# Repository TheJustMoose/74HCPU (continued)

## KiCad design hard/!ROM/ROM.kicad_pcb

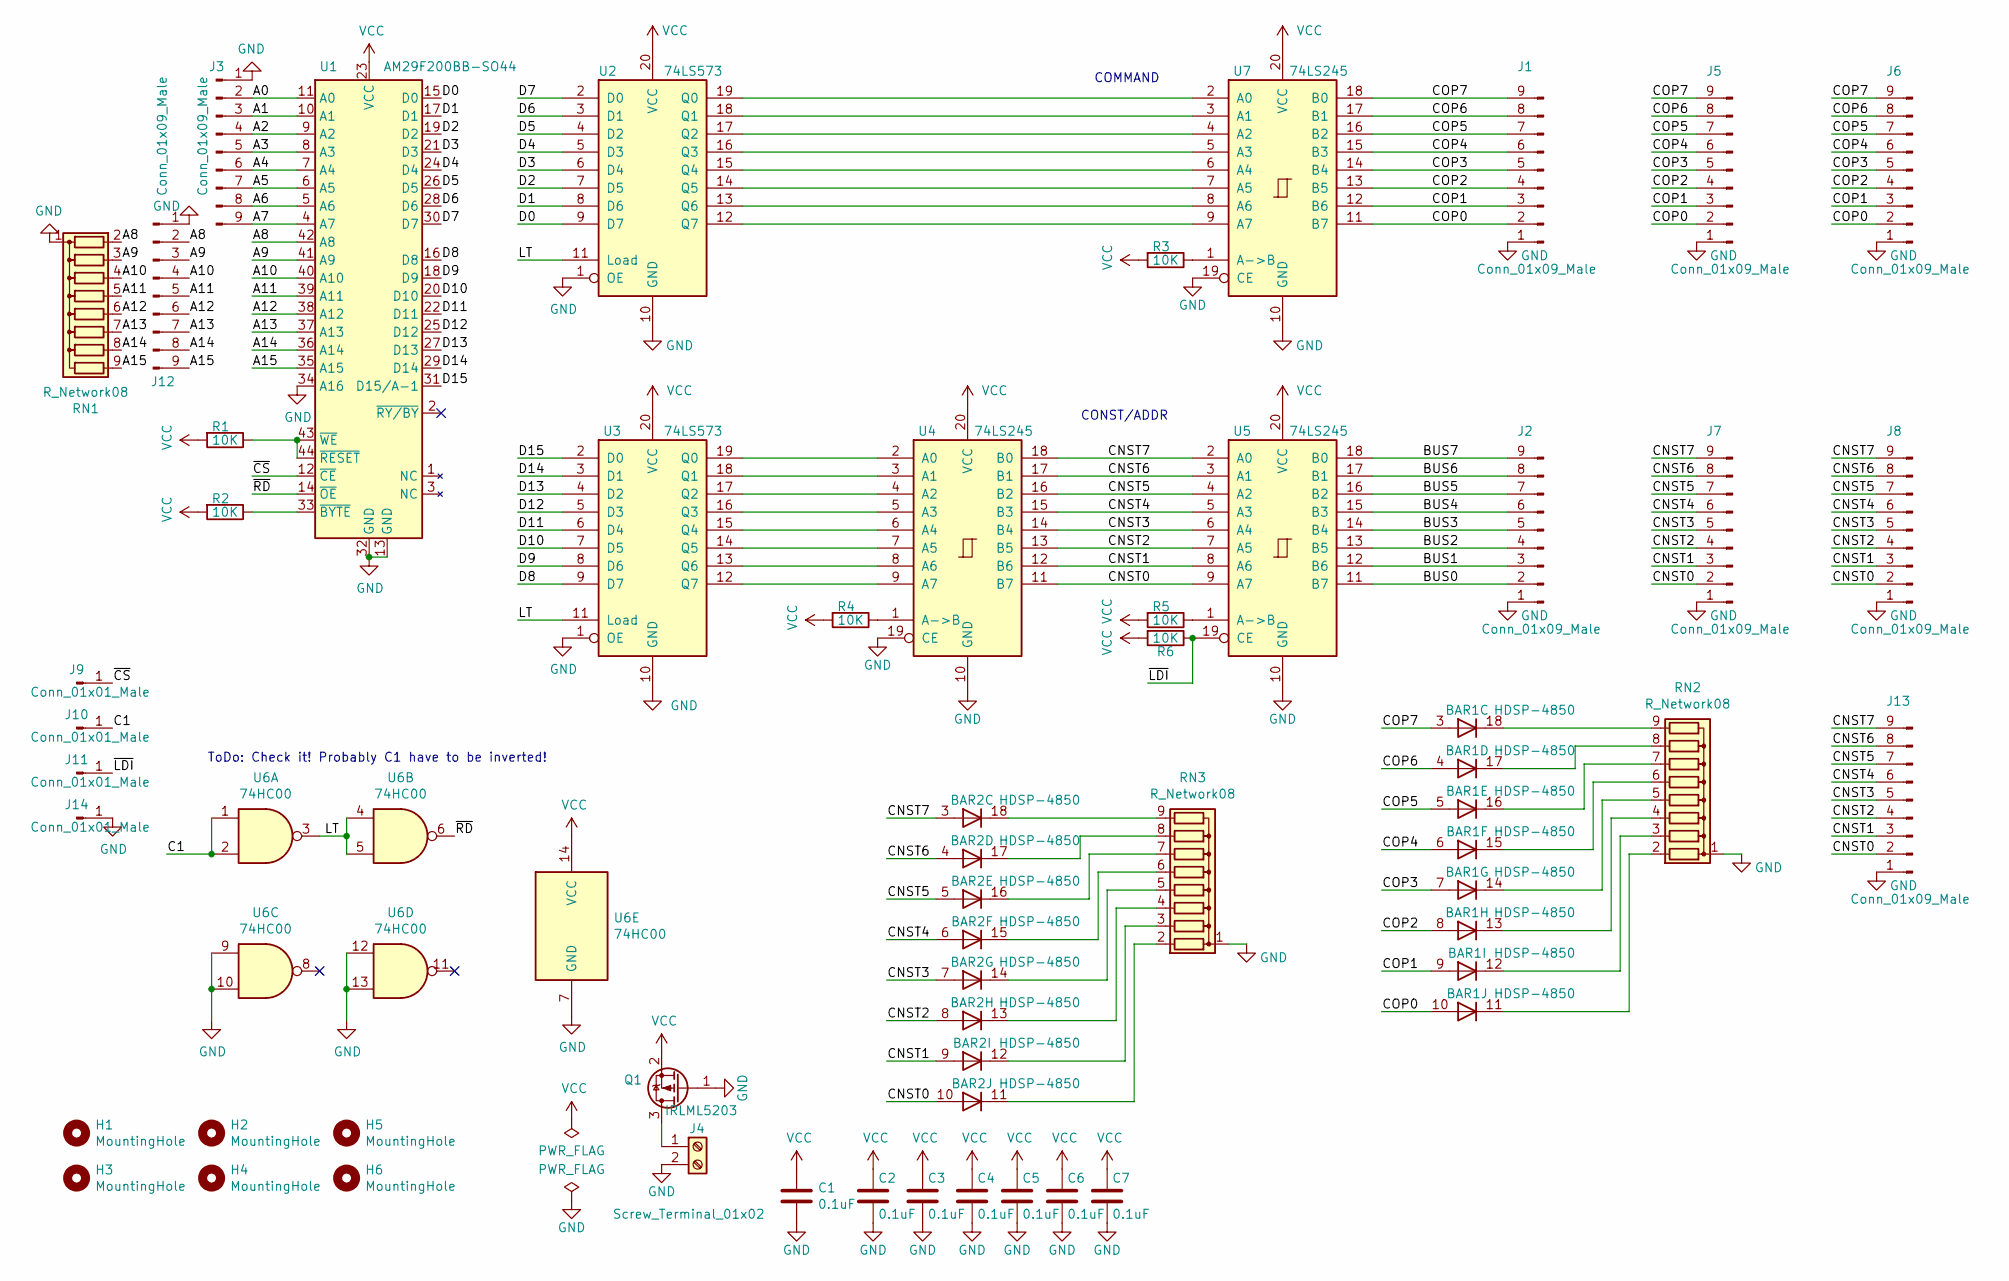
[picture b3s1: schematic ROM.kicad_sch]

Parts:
BAR1, BAR2: HDSP-4850
C1: 0.1uF; C_Rect_L24.0mm_W7.0mm_P22.50mm_MKT
C2, C3, C4, C5, C6, C7: 0.1uF; C_Disc_D7.5mm_W5.0mm_P7.50mm
H1, H2, H3, H4, H5, H6: MountingHole; MountingHole_3.2mm_M3
J1, J2, J3, J5, J6, J7, J8, J12, J13: Conn_01x09_Male; PinHeader_1x09_P2.54mm_Vertical
J4: Screw_Terminal_01x02; TerminalBlock_Phoenix_PT-1,5-2-5.0-H_1x02_P5.00mm_Horizontal
J9, J10, J11, J14: Conn_01x01_Male; PinHeader_1x01_P2.54mm_Vertical
Q1: IRLML5203; SOT-23
R1, R2, R3, R4, R5, R6: 10K; R_0805_2012Metric_Pad1.20x1.40mm_HandSolder
RN1, RN2, RN3: R_Network08; R_Array_SIP9
U1: AM29F200BB-SO44; DIP-44_W15.24mm
U2, U3: 74LS573; DIP-20_W7.62mm
U4, U5, U7: 74LS245; DIP-20_W7.62mm
U6: 74HC00; DIP-14_W7.62mm

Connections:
/A0: J3.2, U1.11 (A0)
/A1: J3.3, U1.10 (A1)
/A2: J3.4, U1.9 (A2)
/A3: J3.5, U1.8 (A3)
/A4: J3.6, U1.7 (A4)
/A5: J3.7, U1.6 (A5)
/A6: J3.8, U1.5 (A6)
/A7: J3.9, U1.4 (A7)
/A8: J12.2, RN1.2 (R1), U1.42 (A8)
/A9: J12.3, RN1.3 (R2), U1.41 (A9)
/A10: J12.4, RN1.4 (R3), U1.40 (A10)
/A11: J12.5, RN1.5 (R4), U1.39 (A11)
/A12: J12.6, RN1.6 (R5), U1.38 (A12)
/A13: J12.7, RN1.7 (R6), U1.37 (A13)
/A14: J12.8, RN1.8 (R7), U1.36 (A14)
/A15: J12.9, RN1.9 (R8), U1.35 (A15)
/BUS0: J2.2, U5.11 (B7)
/BUS1: J2.3, U5.12 (B6)
/BUS2: J2.4, U5.13 (B5)
/BUS3: J2.5, U5.14 (B4)
/BUS4: J2.6, U5.15 (B3)
/BUS5: J2.7, U5.16 (B2)
/BUS6: J2.8, U5.17 (B1)
/BUS7: J2.9, U5.18 (B0)
/C1: J10.1, U6.1, U6.2
/CNST0: BAR2.10 (A), J7.2, J8.2, J13.2, U4.11 (B7), U5.9 (A7)
/CNST1: BAR2.9 (A), J7.3, J8.3, J13.3, U4.12 (B6), U5.8 (A6)
/CNST2: BAR2.8 (A), J7.4, J8.4, J13.4, U4.13 (B5), U5.7 (A5)
/CNST3: BAR2.7 (A), J7.5, J8.5, J13.5, U4.14 (B4), U5.6 (A4)
/CNST4: BAR2.6 (A), J7.6, J8.6, J13.6, U4.15 (B3), U5.5 (A3)
/CNST5: BAR2.5 (A), J7.7, J8.7, J13.7, U4.16 (B2), U5.4 (A2)
/CNST6: BAR2.4 (A), J7.8, J8.8, J13.8, U4.17 (B1), U5.3 (A1)
/CNST7: BAR2.3 (A), J7.9, J8.9, J13.9, U4.18 (B0), U5.2 (A0)
/COP0: BAR1.10 (A), J1.2, J5.2, J6.2, U7.11 (B7)
/COP1: BAR1.9 (A), J1.3, J5.3, J6.3, U7.12 (B6)
/COP2: BAR1.8 (A), J1.4, J5.4, J6.4, U7.13 (B5)
/COP3: BAR1.7 (A), J1.5, J5.5, J6.5, U7.14 (B4)
/COP4: BAR1.6 (A), J1.6, J5.6, J6.6, U7.15 (B3)
/COP5: BAR1.5 (A), J1.7, J5.7, J6.7, U7.16 (B2)
/COP6: BAR1.4 (A), J1.8, J5.8, J6.8, U7.17 (B1)
/COP7: BAR1.3 (A), J1.9, J5.9, J6.9, U7.18 (B0)
/D0: U1.15 (D0), U2.9 (D7)
/D1: U1.17 (D1), U2.8 (D6)
/D2: U1.19 (D2), U2.7 (D5)
/D3: U1.21 (D3), U2.6 (D4)
/D4: U1.24 (D4), U2.5 (D3)
/D5: U1.26 (D5), U2.4 (D2)
/D6: U1.28 (D6), U2.3 (D1)
/D7: U1.30 (D7), U2.2 (D0)
/D8: U1.16 (D8), U3.9 (D7)
/D9: U1.18 (D9), U3.8 (D6)
/D10: U1.20 (D10), U3.7 (D5)
/D11: U1.22 (D11), U3.6 (D4)
/D12: U1.25 (D12), U3.5 (D3)
/D13: U1.27 (D13), U3.4 (D2)
/D14: U1.29 (D14), U3.3 (D1)
/D15: U1.31 (D15/A-1), U3.2 (D0)
/LT: U2.11 (Load), U3.11 (Load), U6.3, U6.4, U6.5
/~CS: J9.1, U1.12 (~CE)
/~LDI: J11.1, R6.1, U5.19 (CE)
/~RD: U1.14 (~OE), U6.6
GND: C1.2, C2.2, C3.2, C4.2, C5.2, C6.2, C7.2, J1.1, J2.1, J3.1, J4.2, J5.1, J6.1, J7.1, J8.1, J12.1, J13.1, J14.1, Q1.1 (G), RN1.1 (common), RN2.1 (common), RN3.1 (common), U1.13 (GND), U1.32 (GND), U1.34 (A16), U2.1 (OE), U2.10 (GND), U3.1 (OE), U3.10 (GND), U4.10 (GND), U4.19 (CE), U5.10 (GND), U6.7 (GND), U6.9, U6.10, U6.12, U6.13, U7.10 (GND), U7.19 (CE)
unnamed: BAR1.11 (K), RN2.2 (R1)
unnamed: BAR1.12 (K), RN2.3 (R2)
unnamed: BAR1.13 (K), RN2.4 (R3)
unnamed: BAR1.14 (K), RN2.5 (R4)
unnamed: BAR1.15 (K), RN2.6 (R5)
unnamed: BAR1.16 (K), RN2.7 (R6)
unnamed: BAR1.17 (K), RN2.8 (R7)
unnamed: BAR1.18 (K), RN2.9 (R8)
unnamed: BAR2.11 (K), RN3.2 (R1)
unnamed: BAR2.12 (K), RN3.3 (R2)
unnamed: BAR2.13 (K), RN3.4 (R3)
unnamed: BAR2.14 (K), RN3.5 (R4)
unnamed: BAR2.15 (K), RN3.6 (R5)
unnamed: BAR2.16 (K), RN3.7 (R6)
unnamed: BAR2.17 (K), RN3.8 (R7)
unnamed: BAR2.18 (K), RN3.9 (R8)
unnamed: J4.1, Q1.3 (D)
unnamed: R1.1, U1.43 (~WE), U1.44 (~RESET)
unnamed: R2.1, U1.33 (~BYTE)
unnamed: R3.1, U7.1 (A->B)
unnamed: R4.1, U4.1 (A->B)
unnamed: R5.1, U5.1 (A->B)
unnamed: U2.12 (Q7), U7.9 (A7)
unnamed: U2.13 (Q6), U7.8 (A6)
unnamed: U2.14 (Q5), U7.7 (A5)
unnamed: U2.15 (Q4), U7.6 (A4)
unnamed: U2.16 (Q3), U7.5 (A3)
unnamed: U2.17 (Q2), U7.4 (A2)
unnamed: U2.18 (Q1), U7.3 (A1)
unnamed: U2.19 (Q0), U7.2 (A0)
unnamed: U3.12 (Q7), U4.9 (A7)
unnamed: U3.13 (Q6), U4.8 (A6)
unnamed: U3.14 (Q5), U4.7 (A5)
unnamed: U3.15 (Q4), U4.6 (A4)
unnamed: U3.16 (Q3), U4.5 (A3)
unnamed: U3.17 (Q2), U4.4 (A2)
unnamed: U3.18 (Q1), U4.3 (A1)
unnamed: U3.19 (Q0), U4.2 (A0)
VCC: C1.1, C2.1, C3.1, C4.1, C5.1, C6.1, C7.1, Q1.2 (S), R1.2, R2.2, R3.2, R4.2, R5.2, R6.2, U1.23 (VCC), U2.20 (VCC), U3.20 (VCC), U4.20 (VCC), U5.20 (VCC), U6.14 (VCC), U7.20 (VCC)

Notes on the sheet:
CONST/ADDR
ToDo: Check it! Probably C1 have to be inverted!
COMMAND

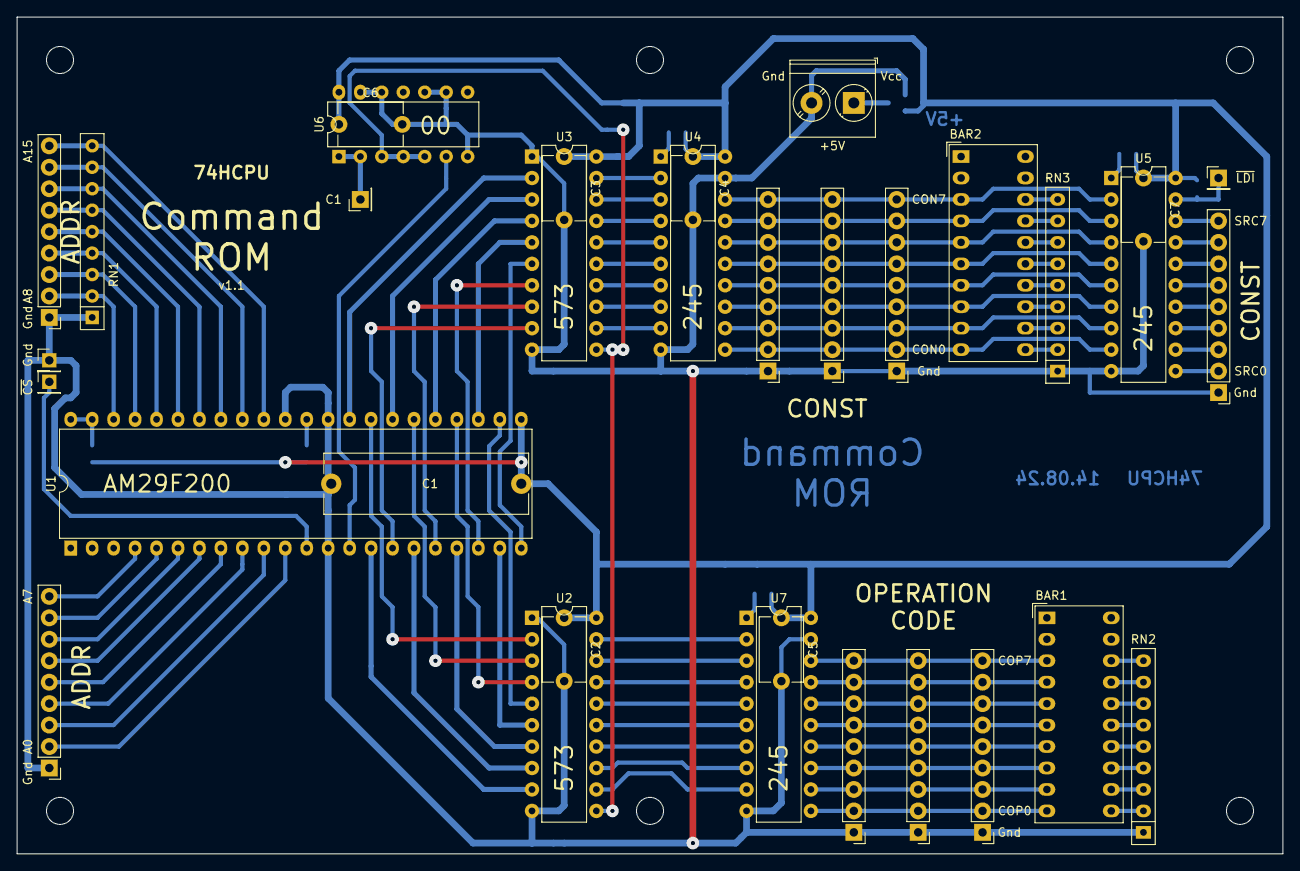
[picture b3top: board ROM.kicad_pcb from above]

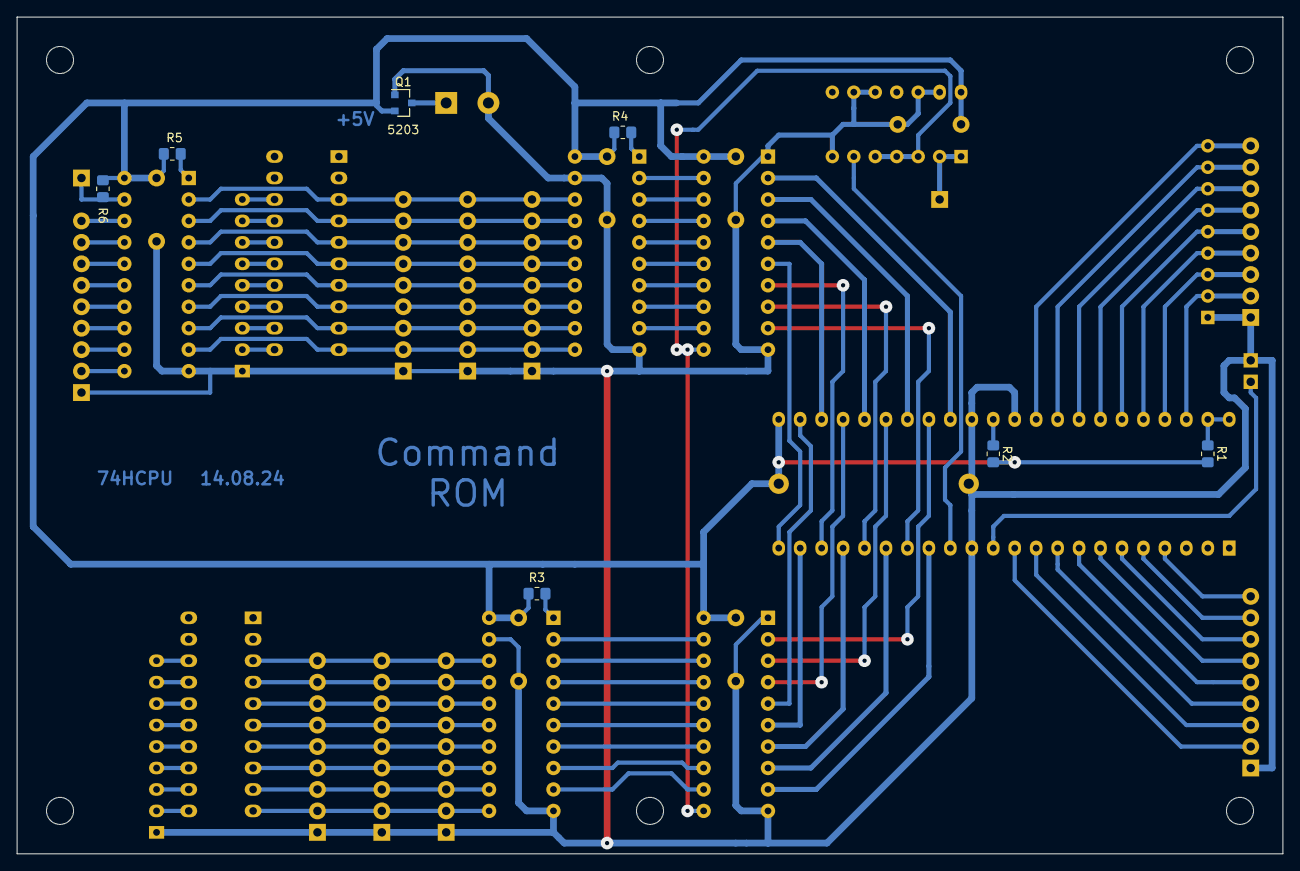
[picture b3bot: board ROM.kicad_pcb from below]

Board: 2 copper layers, 149.9 x 99.1 mm, 46 parts (7 on the bottom side), 101 nets.

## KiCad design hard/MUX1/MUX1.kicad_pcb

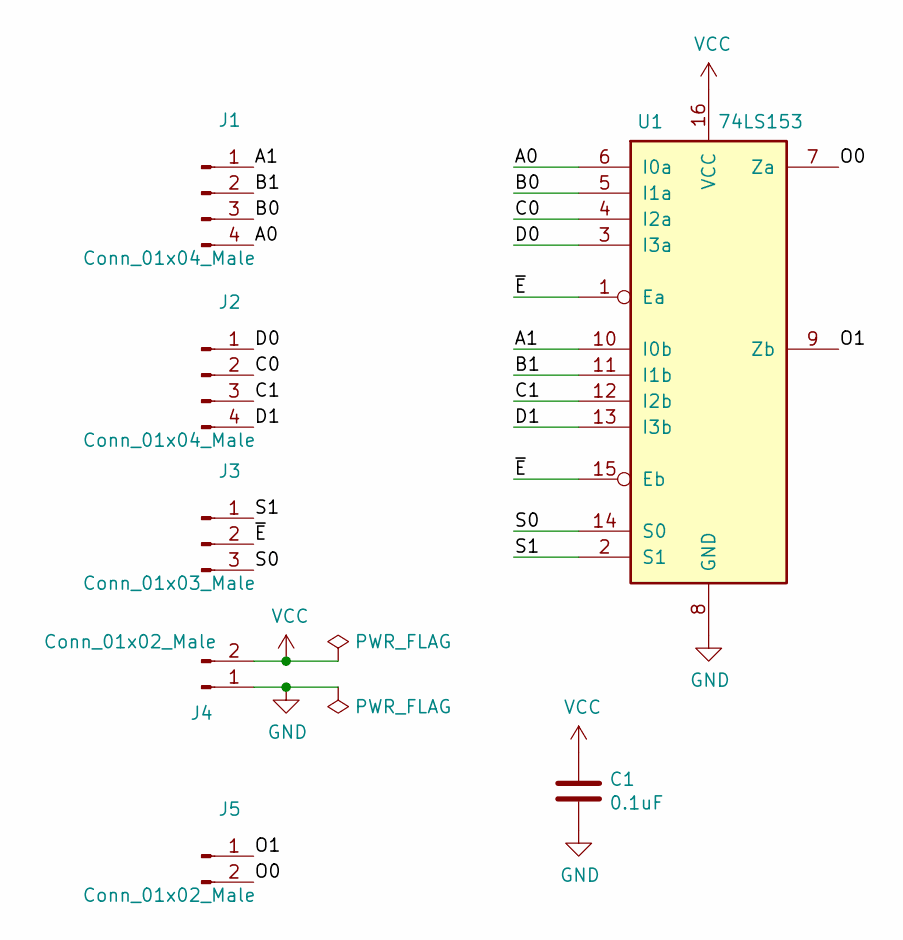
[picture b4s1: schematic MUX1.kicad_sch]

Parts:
C1: 0.1uF; C_0805_2012Metric_Pad1.18x1.45mm_HandSolder
J1, J2: Conn_01x04_Male; PinHeader_1x04_P2.54mm_Horizontal
J3: Conn_01x03_Male; PinHeader_1x03_P2.54mm_Horizontal
J4, J5: Conn_01x02_Male; PinHeader_1x02_P2.54mm_Horizontal
U1: 74LS153; SO-16_3.9x9.9mm_P1.27mm

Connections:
/A0: J1.4, U1.6 (I0a)
/A1: J1.1, U1.10 (I0b)
/B0: J1.3, U1.5 (I1a)
/B1: J1.2, U1.11 (I1b)
/C0: J2.2, U1.4 (I2a)
/C1: J2.3, U1.12 (I2b)
/D0: J2.1, U1.3 (I3a)
/D1: J2.4, U1.13 (I3b)
/O0: J5.2, U1.7 (Za)
/O1: J5.1, U1.9 (Zb)
/S0: J3.3, U1.14 (S0)
/S1: J3.1, U1.2 (S1)
/~E: J3.2, U1.1 (Ea), U1.15 (Eb)
GND: C1.2, J4.1, U1.8 (GND)
VCC: C1.1, J4.2, U1.16 (VCC)

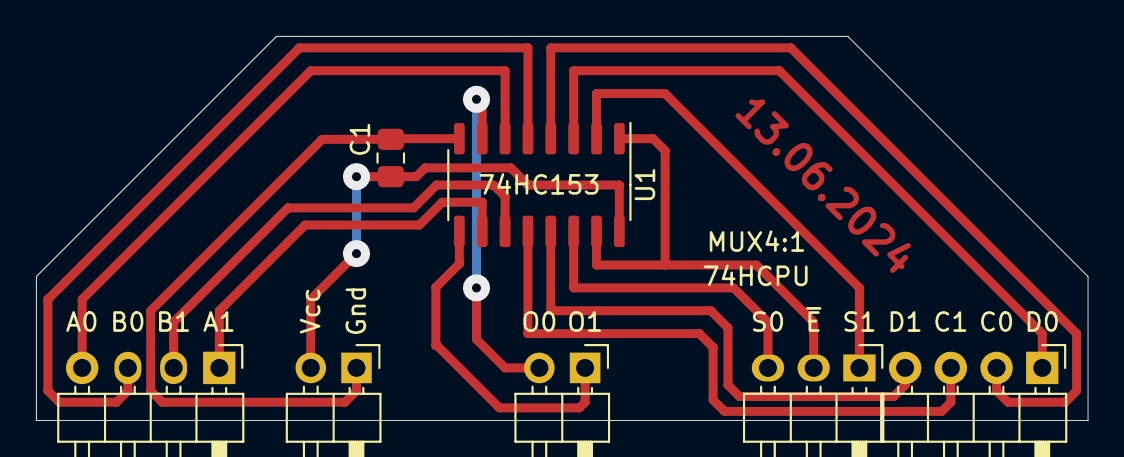
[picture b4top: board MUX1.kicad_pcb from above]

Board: 2 copper layers, 58.4 x 21.3 mm, 7 parts (0 on the bottom side), 15 nets.

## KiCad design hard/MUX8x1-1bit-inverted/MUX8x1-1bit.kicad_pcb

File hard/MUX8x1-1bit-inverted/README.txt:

This mux have inverted order of D0..D7!

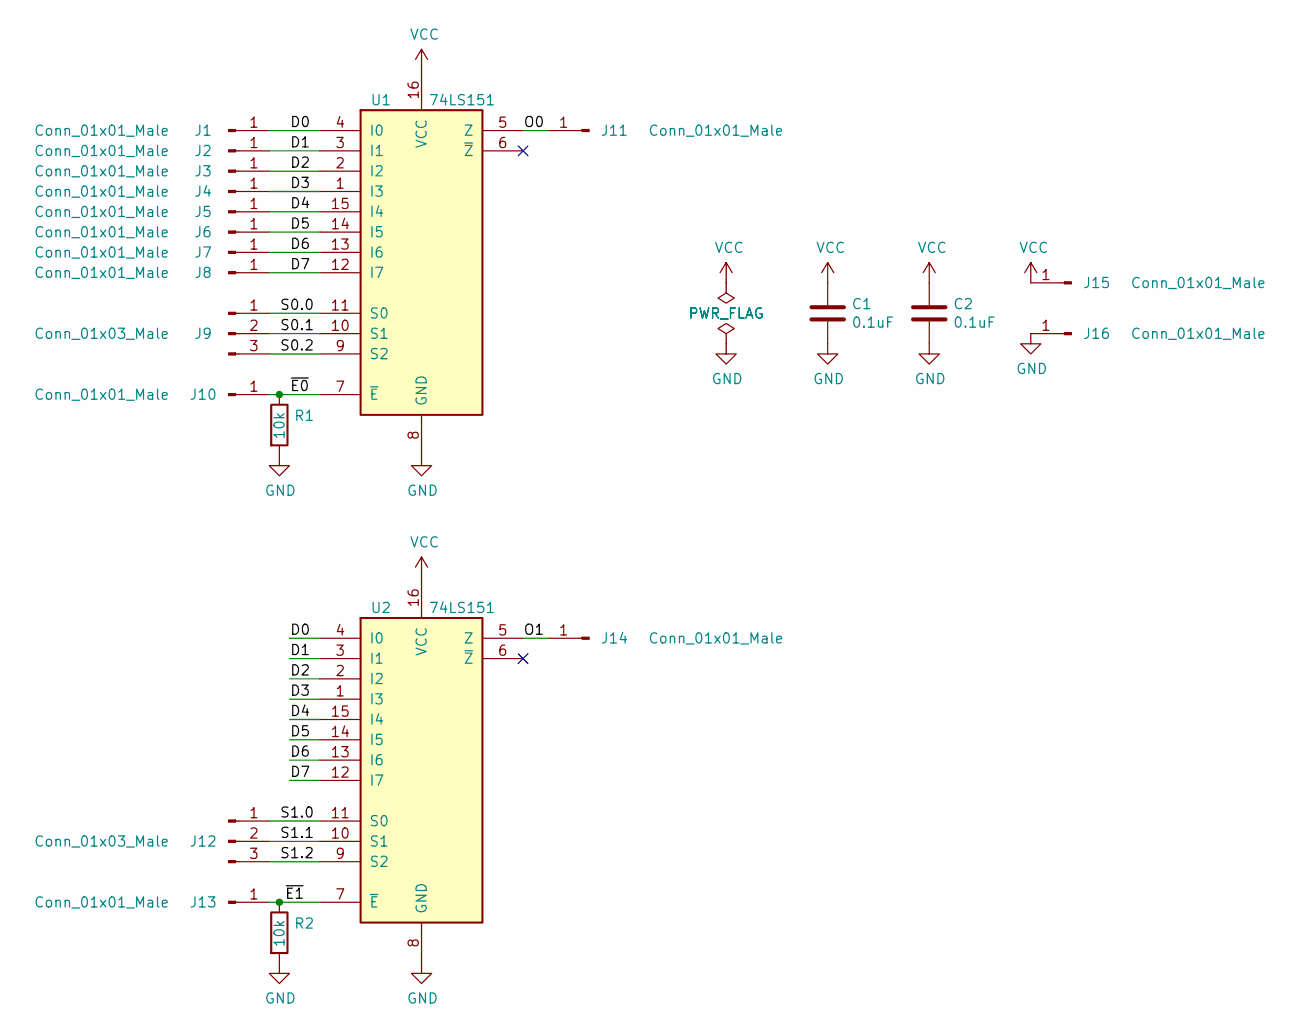
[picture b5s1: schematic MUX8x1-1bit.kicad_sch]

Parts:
C1, C2: 0.1uF; C_0805_2012Metric_Pad1.18x1.45mm_HandSolder
J1, J2, J3, J4, J5, J6, J7, J8, J10, J11, J13, J14, J15, J16: Conn_01x01_Male; PinHeader_1x01_P2.54mm_Horizontal
J9, J12: Conn_01x03_Male; PinHeader_1x03_P2.54mm_Horizontal
R1, R2: 10k; R_0805_2012Metric_Pad1.20x1.40mm_HandSolder
U1, U2: 74LS151; SO-16_3.9x9.9mm_P1.27mm

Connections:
/D0: J1.1, U1.4 (I0), U2.4 (I0)
/D1: J2.1, U1.3 (I1), U2.3 (I1)
/D2: J3.1, U1.2 (I2), U2.2 (I2)
/D3: J4.1, U1.1 (I3), U2.1 (I3)
/D4: J5.1, U1.15 (I4), U2.15 (I4)
/D5: J6.1, U1.14 (I5), U2.14 (I5)
/D6: J7.1, U1.13 (I6), U2.13 (I6)
/D7: J8.1, U1.12 (I7), U2.12 (I7)
/O0: J11.1, U1.5 (Z)
/O1: J14.1, U2.5 (Z)
/S0.0: J9.1, U1.11 (S0)
/S0.1: J9.2, U1.10 (S1)
/S0.2: J9.3, U1.9 (S2)
/S1.0: J12.1, U2.11 (S0)
/S1.1: J12.2, U2.10 (S1)
/S1.2: J12.3, U2.9 (S2)
/~E0: J10.1, R1.1, U1.7 (~E)
/~E1: J13.1, R2.1, U2.7 (~E)
GND: C1.2, C2.2, J16.1, R1.2, R2.2, U1.8 (GND), U2.8 (GND)
VCC: C1.1, C2.1, J15.1, U1.16 (VCC), U2.16 (VCC)

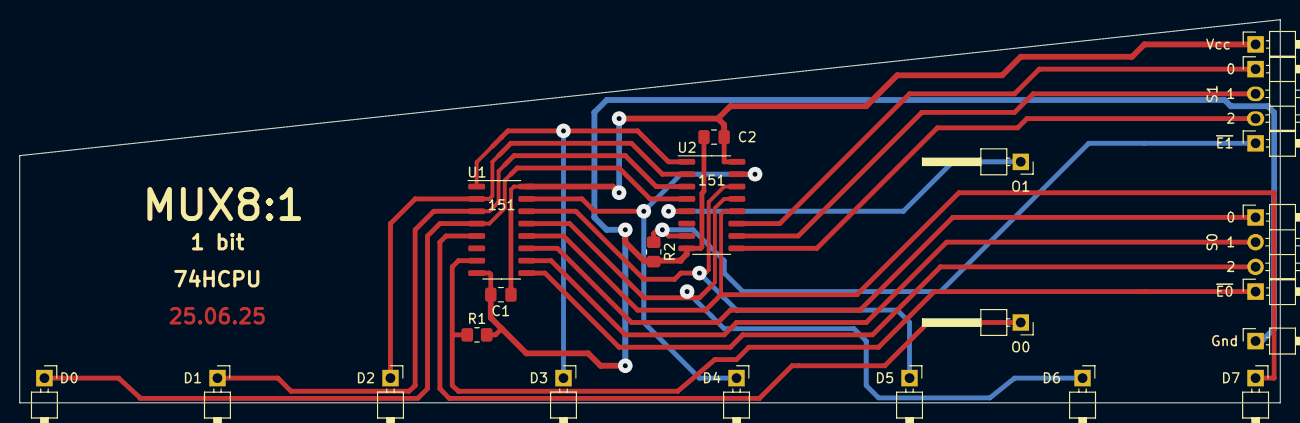
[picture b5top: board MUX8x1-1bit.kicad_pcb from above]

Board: 2 copper layers, 129.5 x 39.4 mm, 22 parts (0 on the bottom side), 20 nets.
